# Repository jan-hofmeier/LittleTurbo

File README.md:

# Little Turbo

This card plugs into the co-processor slot of the Amiga 2000 and allows you to clock your 68000 or 68010 at 14Mhz. It also supports 2MB of SRAM of wich up to 1.75MB can be used as Fast Ranger RAM, like the Memory card of the original German A2000. The SRAM can run at the full 14Mhz with zero wait states.
It can also serve just as an Memory Expansion, without the 14Mhz stuff. In this case the CPU can stay in the sockel of the mainboard
The memory is mapped at `$C0000`. If you have a Rev. 4 B2000 this will overlap the onboard 512K "Slow RAM". 
The unused Part of the 2MB of SRAM can be used to emulate a Kickstart ROM up to 1MB.

The Layout of the Slot Connector was taken from SukkoPera OpenAmiga2000CoproAdapter

### State of the Project

The PCB is done, next up is verifying that it works as intended.

### Installation
**Please be very careful when plugging this board** in the co-processor slot: there is an arrow on the board, **it must point to the back of the Amiga**. Plugging this adapter backwards will damage your CPU/accelerator card, as some pins of the CPU slot carry +12V!

### Parts
https://www.digikey.de/short/4795fv

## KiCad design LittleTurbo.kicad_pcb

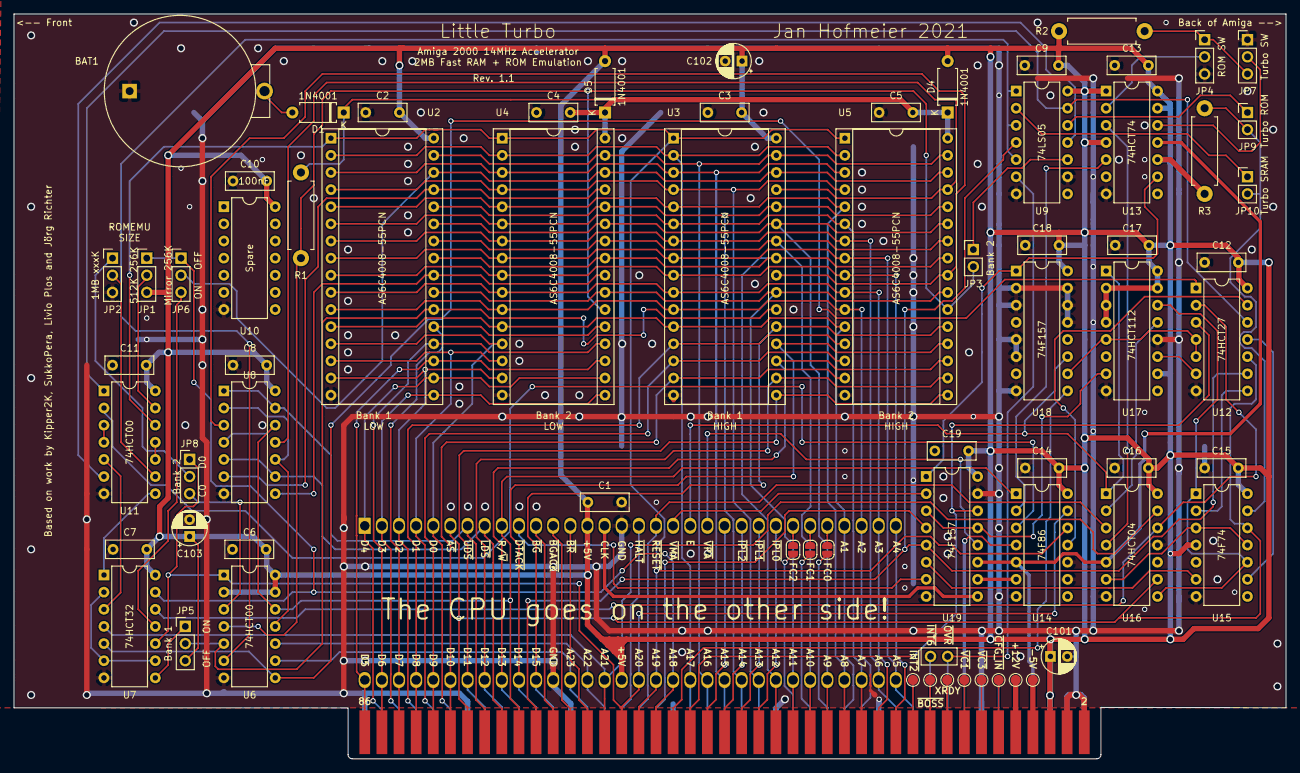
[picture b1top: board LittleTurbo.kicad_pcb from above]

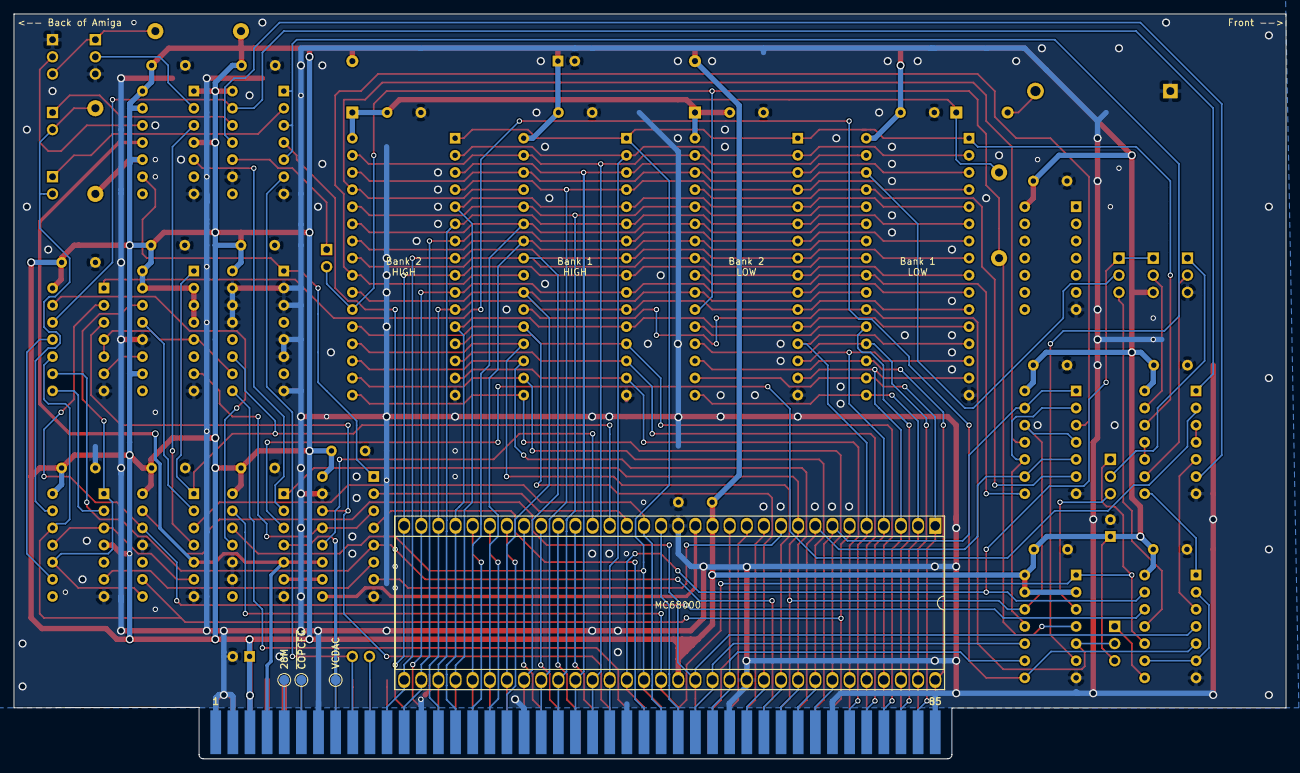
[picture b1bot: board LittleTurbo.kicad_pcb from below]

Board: 2 copper layers, 188.6 x 110.4 mm, 75 parts (5 on the bottom side), 131 nets.

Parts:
BAT1: BS-7; Battery_Holder_Coin_2032_BS-7
C1, C2, C3, C4, C5, C6, C7, C8, C9, C10, C11, C12, C13, C14, C15, C16, C17, C18, C19: 100nF; C_Disc_D7.0mm_W2.5mm_P5.00mm
C101, C102, C103: 47uF; CP_Radial_D5.0mm_P2.50mm
CN1: A2000_COPRO_SLOT
D1, D4, D5: 1N4001; D_A-405_P7.62mm_Horizontal
JP1: 512K 256K; PinHeader_1x03_P2.54mm_Vertical
JP2: 1MB xxxK; PinHeader_1x03_P2.54mm_Vertical
JP3: Bank 2; PinHeader_1x02_P2.54mm_Vertical
JP4: ROM SW; PinHeader_1x03_P2.54mm_Vertical
JP5: Bank 1; PinHeader_1x03_P2.54mm_Vertical
JP6: Mirror 256K; PinHeader_1x03_P2.54mm_Vertical
JP7: Turbo SW; PinHeader_1x03_P2.54mm_Vertical
JP8: Bank2 D0_C0; PinHeader_1x03_P2.54mm_Vertical
JP9: Turbo ROM; PinHeader_1x02_P2.54mm_Vertical
JP10: Turbo SRAM; PinHeader_1x02_P2.54mm_Vertical
P1: CONN_2; PinHeader_1x02_P2.54mm_Vertical
P2, P3, P4: CONN_2; SolderJumper-2_P1.3mm_Open_RoundedPad1.0x1.5mm
P5, P6, P7, P8, P9, P10, P11, P12, P13, P14, P15: CONN_1; TestPoint_Pad_D1.5mm
P99: OSHW_LOGO; OSHW-Logo_7.5x8mm_Copper
R1, R2, R3: 500; R_Axial_DIN0411_L9.9mm_D3.6mm_P12.70mm_Horizontal
U1: 68000D; DIP-64_W22.86mm_Socket_LongPads
U2, U3, U4, U5: AS6C4008-55PCN; DIP-32_W15.24mm_Socket
U6, U11: 74HCT00; DIP-14_W7.62mm
U7, U8: 74HCT32; DIP-14_W7.62mm
U9: 74LS05; DIP-14_W7.62mm
U10: Spare; DIP-14_W7.62mm
U12: 74HCT27; DIP-14_W7.62mm
U13: 74HCT74; DIP-14_W7.62mm
U14: 74F86; DIP-14_W7.62mm
U15: 74F74; DIP-14_W7.62mm
U16: 74HCT04; DIP-14_W7.62mm
U17: 74HCT112; DIP-16_W7.62mm
U18, U19: 74F157; DIP-16_W7.62mm

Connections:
5VR: JP4.1, JP7.3, R2.2
+5V: C1.1, C2.2, C3.2, C6.1, C7.1, C8.1, C9.1, C10.1, C11.1, C12.1, C13.1, C14.1, C15.1, C16.1, C17.1, C18.1, C19.1, C101.1, C102.1, C103.1, CN1.5, CN1.6, D4.2, D5.2, JP1.3, JP5.3, R2.1, R3.1, U1.14, U1.49, U2.32, U3.32, U6.2, U6.13, U6.14, U7.14, U8.14, U9.14, U10.14, U11.14, U12.14, U13.1, U13.4, U13.10, U13.13, U13.14, U14.14, U15.4, U15.14, U16.14, U17.2, U17.3, U17.4, U17.10, U17.15, U17.16, U18.16, U19.16
+12V: CN1.10, P15.1
-5V: CN1.8, P14.1
/CPU_CLK: U1.15, U19.9
/Memory/ROMEN: U9.13, U11.1, U12.12
/Memory/ROMR~W: JP4.2, U13.2
/Memory/SROMON: U11.2, U14.3
/Memory/VSRAM: C4.2, C5.2, D1.1, D4.1, D5.1, R1.2, U4.32, U5.32
/Memory/a18m: JP6.2, U2.30, U3.30, U4.30, U5.30
/Memory/~CRAM: U7.2, U7.6, U7.9
/Memory/~CS1: JP5.2, U2.22, U3.22, U6.5
/Memory/~CS2: JP3.2, R1.1, U4.22, U5.22, U6.4
/Memory/~DTACK_FAST: JP9.2, JP10.2, R3.2, U15.13
/Memory/~HIGH: U6.8, U7.5, U12.1
/Memory/~LOE: U2.24, U4.24, U8.8
/Memory/~LWE: U2.29, U4.29, U8.6
/Memory/~OE: U6.11, U8.2, U8.10
/Memory/~OVR: CN1.17, P1.2, U9.6
/Memory/~RAM2: U7.3, U11.5
/Memory/~ROMEN: JP9.1, U9.12
/Memory/~SROM: U11.3, U11.4
/Memory/~UOE: U3.24, U5.24, U8.3
/Memory/~UWE: U3.29, U5.29, U8.11
/Memory/~a21: U7.12, U12.2, U16.12
/Turbo/14M: U14.6, U19.10
/Turbo/CDAC: CN1.15, P7.1, U14.4
/Turbo/E_CPU: U1.20, U16.1, U17.1, U18.11
/Turbo/~DTACK_CPU: U1.10, U19.7
/Turbo/~VMA_CPU: U1.19, U19.2
/Turbo/~VPA_CPU: U1.21, U19.12
/a1: CN1.29, U1.29, U2.12, U3.12, U4.12, U5.12
/a2: CN1.27, U1.30, U2.11, U3.11, U4.11, U5.11
/a3: CN1.26, U1.31, U2.10, U3.10, U4.10, U5.10
/a4: CN1.24, U1.32, U2.9, U3.9, U4.9, U5.9
/a5: CN1.21, U1.33, U2.8, U3.8, U4.8, U5.8
/a6: CN1.23, U1.34, U2.7, U3.7, U4.7, U5.7
/a7: CN1.28, U1.35, U2.6, U3.6, U4.6, U5.6
/a8: CN1.30, U1.36, U2.5, U3.5, U4.5, U5.5
/a9: CN1.32, U1.37, U2.27, U3.27, U4.27, U5.27
/a10: CN1.34, U1.38, U2.26, U3.26, U4.26, U5.26
/a11: CN1.36, U1.39, U2.23, U3.23, U4.23, U5.23
/a12: CN1.38, U1.40, U2.25, U3.25, U4.25, U5.25
/a13: CN1.39, U1.41, U2.4, U3.4, U4.4, U5.4
/a14: CN1.41, U1.42, U2.28, U3.28, U4.28, U5.28
/a15: CN1.43, U1.43, U2.3, U3.3, U4.3, U5.3
/a16: CN1.45, U1.44, U2.31, U3.31, U4.31, U5.31
/a17: CN1.47, U1.45, U2.2, U3.2, U4.2, U5.2
/a18: CN1.52, JP1.1, JP6.1, U1.46, U7.13
/a19: CN1.54, U1.47, U2.1, U3.1, U4.1, U5.1, U11.12, U14.12
/a20: CN1.56, JP8.1, U1.48, U6.1, U7.10, U14.13
/a21: CN1.58, U1.50, U7.4, U16.13
/a22: CN1.57, U1.51, U6.10
/a23: CN1.59, U1.52, U6.9
/d0: CN1.75, U1.5, U2.13, U4.13
/d1: CN1.77, U1.4, U2.14, U4.14
/d2: CN1.79, U1.3, U2.15, U4.15
/d3: CN1.81, U1.2, U2.17, U4.17
/d4: CN1.83, U1.1, U2.18, U4.18
/d5: CN1.86, U1.64, U2.19, U4.19
/d6: CN1.84, U1.63, U2.20, U4.20
/d7: CN1.82, U1.62, U2.21, U4.21
/d8: CN1.80, U1.61, U3.13, U5.13
/d9: CN1.78, U1.60, U3.14, U5.14
/d10: CN1.76, U1.59, U3.15, U5.15
/d11: CN1.71, U1.58, U3.17, U5.17
/d12: CN1.69, U1.57, U3.18, U5.18
/d13: CN1.67, U1.56, U3.19, U5.19
/d14: CN1.65, U1.55, U3.20, U5.20
/d15: CN1.63, U1.54, U3.21, U5.21
/e: CN1.50, U18.9
/fc0: CN1.31, P4.1
/fc1: CN1.33, P3.1
/fc2: CN1.35, P2.1
/r_~w: CN1.68, U1.9, U6.12, U8.4, U8.12, U14.1
/v7m: CN1.7, U13.11, U14.5, U16.5, U19.11
/~as: CN1.74, U1.6, U12.10, U15.12, U16.9
/~berr: CN1.46, U1.22
/~bgack: CN1.62, U1.12
/~cbg: CN1.64, U1.11
/~cbr: CN1.60, U1.13
/~dtack: CN1.66, U9.4, U12.9, U19.5
/~hlt: CN1.55, U1.17
/~ipl0: CN1.40, U1.25
/~ipl1: CN1.42, U1.24
/~ipl2: CN1.44, U1.23
/~lds: CN1.70, U1.8, U8.5, U8.9
/~rst: CN1.53, U1.18, U16.3
/~uds: CN1.72, U1.7, U8.1, U8.13
/~vma: CN1.51, U19.4
/~vpa: CN1.48, U12.3, U19.14
GND: BAT1.Neg, C1.2, C2.1, C3.1, C4.1, C5.1, C6.2, C7.2, C8.2, C9.2, C10.2, C11.2, C12.2, C13.2, C14.2, C15.2, C16.2, C17.2, C18.2, C19.2, C101.2, C102.2, C103.2, CN1.1, CN1.2, CN1.3, CN1.4, CN1.13, CN1.25, CN1.37, CN1.49, CN1.61, CN1.73, CN1.85, JP2.3, JP4.3, JP7.1, U1.16, U1.53, U2.16, U3.16, U4.16, U5.16, U6.7, U7.7, U8.7, U9.7, U9.9, U10.7, U11.7, U12.7, U13.7, U14.7, U14.9, U14.10, U15.7, U16.7, U16.11, U17.8, U17.12, U18.2, U18.3, U18.5, U18.6, U18.8, U18.13, U18.14, U18.15, U19.8, U19.15
unnamed: BAT1.Pos, D1.2
unnamed: CN1.9, P5.1
unnamed: CN1.11, P6.1
unnamed: CN1.12, P8.1
unnamed: CN1.14, P9.1
unnamed: CN1.16, P10.1
unnamed: CN1.18, P11.1
unnamed: CN1.19, P1.1
unnamed: CN1.20, P12.1
unnamed: CN1.22, P13.1
unnamed: JP1.2, U11.13
unnamed: JP2.1, JP8.2
unnamed: JP2.2, U11.9
unnamed: JP3.1, U9.10
unnamed: JP5.1, U7.8
unnamed: JP6.3, U7.11
unnamed: JP7.2, U13.12
unnamed: JP8.3, U6.3
unnamed: JP10.1, U9.2
unnamed: P2.2, U1.26
unnamed: P3.2, U1.27
unnamed: P4.2, U1.28
unnamed: U6.6, U9.1, U9.3, U9.5
unnamed: U9.11, U11.6
unnamed: U7.1, U11.8
unnamed: U11.10, U11.11
unnamed: U12.4, U12.5, U17.5, U18.10
unnamed: U12.6, U17.11
unnamed: U12.8, U15.2
unnamed: U12.11, U15.9
unnamed: U12.13, U14.11
unnamed: U13.3, U16.4
unnamed: U13.5, U14.2
unnamed: U13.9, U18.1, U19.1
unnamed: U15.1, U15.10, U16.8, U17.14
unnamed: U15.6, U19.6
unnamed: U15.3, U15.11, U16.6
unnamed: U16.2, U17.13
unnamed: U17.7, U19.3, U19.13

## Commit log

2021-01-02 update gitignore
2021-01-02 Memory bank 1
2021-01-02 rearange stuff
2021-01-02 decode second bank
2021-01-02 rom emulation bank
2021-01-02 jumper for rom size
2021-01-02 swap upper and lower memory byte on pcb
2021-01-02 add battery
2021-01-02 simplyfy
2021-01-02 rearange
2021-01-02 more rearange
2021-01-02 romen
2021-01-03 ROM RW switch
2021-01-03 replace 2 ORs by 3 way OR to share the IC
2021-01-03 RST low active
2021-01-03 reorganize components for partial builds
2021-01-03 add jumpers to disable memory banks
2021-01-03 remove wrong connection
2021-01-03 wire the jumper up correctly
2021-01-03 add jumper to map second bank at C0000
2021-01-03 cleanup
2021-01-04 cleaning up a bit more
2021-01-04 Turbo Sheet
2021-01-04 finish turbo section
2021-01-04 component names
2021-01-04 capacitors for memory
2021-01-04 add electrolytics
2021-01-04 sheet metadata
2021-01-04 assign footprints
2021-01-06 align to 10mil
2021-01-06 routed upper byte
2021-01-06 routes
2021-01-07 new layout
2021-01-07 more routing
2021-01-07 routed address decoding
2021-01-08 turbo layout
2021-01-08 finish routing
2021-01-08 add missing routes
2021-01-08 fill areas
2021-01-08 morevias
2021-01-08 more ground
2021-01-09 fix unconnected
2021-01-09 fix drc warnings
2021-01-09 fix incorrect courtyard of connector
2021-01-09 fix unconnected ground
2021-01-09 silk screen
2021-01-10 get symbols from submodule
2021-01-10 rom mirror
2021-01-10 dont mirror in lower 512k
2021-01-10 fix connector and small stuff
2021-01-11 visuals
2021-01-11 fix bug with using second bank at C0
2021-01-14 new adress decoding for bank2
2021-01-15 update routes
2021-01-15 reorganize turbo jumpers
2021-01-15 fix connector
2021-01-15 update silk screen
2021-01-15 shrink board
2021-01-15 remove via
2021-01-15 move track
2021-01-15 description
2021-01-15 add revision
2021-01-15 track clearence
2021-01-15 clean a few tracks
2021-01-16 fix 265k rom in schematics
2021-01-16 apply fix to pcb
2021-01-16 clean up
2021-01-16 remove explicit ground connections
2021-01-16 more cleanup
2021-01-16 add protection resistor
2021-01-16 generate gerbers
2021-01-17 some minor stuff
2021-01-17 updated gerbers
2021-01-18 add parts from digikey
2021-01-18 use digikey battery holder
2021-01-18 print component values on silk
2021-01-18 fix unconnected via
2021-01-19 remove a few vias via
2021-01-19 more via fixing
2021-01-19 Update Parts list
2021-01-24 render
2021-01-24 Add render to Readme
2021-02-03 fix silkscreen label
2021-02-04 fix uds lds mixup
2021-02-04 turn jumper around so it matches silk screen
2021-02-12 rename project files to Little Turbo
2021-02-12 new turbo schematics
2021-07-18 something
2021-07-19 add Memory fixes to schematics
2021-07-19 generate 7M from cdac schematics
2021-07-19 use not cdac to invert 14M schematics
2021-07-19 fix shee input schematics
2021-07-21 new DTACK delay in schematics
2021-07-21 AS UDS LDS delay in schematics
2021-07-24 delay BG
2021-07-27 pins

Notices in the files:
LittleTurbo.kicad_pcb:
Licensed under CERN OHL v.1.2
CERN OHL v.1.2
